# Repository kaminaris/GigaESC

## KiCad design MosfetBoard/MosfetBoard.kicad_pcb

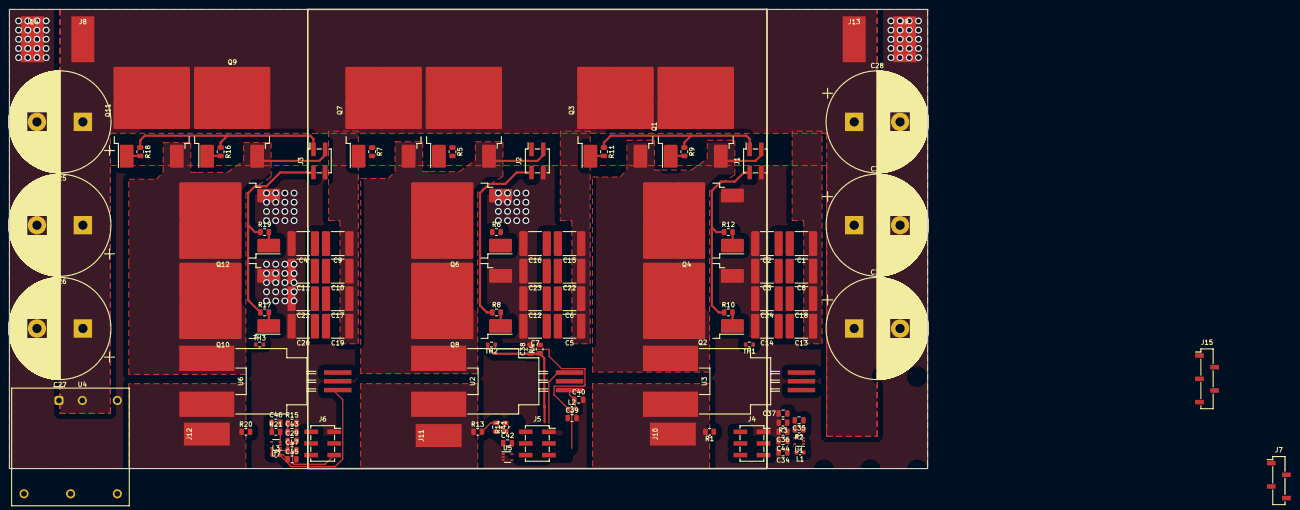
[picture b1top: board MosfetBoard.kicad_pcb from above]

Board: 2 copper layers, 200.0 x 100.0 mm, 106 parts (0 on the bottom side), 58 nets.

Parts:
C1, C2, C3, C4, C5, C6, C7, C8, C9, C10, C11, C12, C13, C14, C15, C16, C17, C18, C19, C20, C21, C22, C23, C24: C; C_2220_5650Metric
C25, C26, C27, C28, C30, C31: 680uF 200V; CP_Radial_D22.0mm_P10.00mm_SnapIn
C29, C35, C36, C39, C41, C42, C44, C46, C47: 100nF; C_0805_2012Metric
C34, C40, C45: 2.2u; C_0805_2012Metric
C37, C38, C43: 1u; C_0805_2012Metric
J1: DRIVER1; PinSocket_2x02_P2.54mm_Vertical_SMD
J2: DRIVER2; PinSocket_2x02_P2.54mm_Vertical_SMD
J3: DRIVER3; PinSocket_2x02_P2.54mm_Vertical_SMD
J4: PhaseConn1; PinSocket_2x03_P2.54mm_Vertical_SMD
J5: PhaseConn2; PinSocket_2x03_P2.54mm_Vertical_SMD
J6: PhaseConn3; PinSocket_2x03_P2.54mm_Vertical_SMD
J7: VINConn; PinSocket_1x04_P2.54mm_Vertical_SMD_Pin1Left
J8: BATT+Conn1; SolderWirePad_1x01_SMD_5x10mm
J9: BATT-Conn1; SolderWirePad_1x01_SMD_5x10mm
J10: A_PAD; SolderWirePad_1x01_SMD_5x10mm
J11: B_PAD; SolderWirePad_1x01_SMD_5x10mm
J12: C_PAD; SolderWirePad_1x01_SMD_5x10mm
J13: BATT+Conn2; SolderWirePad_1x01_SMD_5x10mm
J14: BATT-Conn2; SolderWirePad_1x01_SMD_5x10mm
J15: AuxConn; PinSocket_1x05_P2.54mm_Vertical_SMD_Pin1Left
L1, L2, L3: BLM18HE152SN1D; L_0603_1608Metric
Q1, Q2, Q3, Q4, Q5, Q6, Q7, Q8, Q9, Q10, Q11, Q12: IXTT220N20X4HV; TO-268-2
R1, R13, R20: 150k; R_0805_2012Metric
R2, R14, R21: 2.7k; R_0805_2012Metric
R3, R4, R15: 10k; R_0805_2012Metric
R5, R6, R7, R8, R9, R10, R11, R12, R16, R17, R18, R19: 2r2; R_0805_2012Metric
TH1, TH2, TH3: NCP18XH103F03RB; R_0603_1608Metric
U1, U5, U7: RS2166XC5; SOT-353_SC-70-5
U2, U3, U6: ACS773ECB-200B-PFF-T; Allegro_CB_SMD
U4: RDE20110S12; Converter_DCDC_TRACO_THN30-xxxx_THT

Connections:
+3.3V: C29.1, C36.1, C39.1, C42.1, C44.1, C47.1, J4.5, J5.5, J6.5, L1.1, L2.1, L3.1, TH1.1, TH2.1, TH3.1, U1.5 (VCC), U5.5 (VCC), U7.5 (VCC)
+12V: J7.3, J7.4
+BATT: C1.1, C5.1, C6.1, C8.1, C9.1, C10.1, C13.1, C15.1, C17.1, C18.1, C19.1, C22.1, C25.1, C26.1, C27.1, C28.1, C30.1, C31.1, J8.1, J13.1, Q1.2 (D), Q3.2 (D), Q5.2 (D), Q7.2 (D), Q9.2 (D), Q11.2 (D), U4.1 (+Vin)
-BATT: C2.2, C3.2, C4.2, C7.2, C11.2, C12.2, C14.2, C16.2, C20.2, C21.2, C23.2, C24.2, C25.2, C26.2, C27.2, C28.2, C29.2, C30.2, C31.2, C34.2, C36.2, C37.2, C38.2, C39.2, C40.2, C42.2, C43.2, C44.2, C45.2, C47.2, J1.4, J2.4, J3.4, J4.1, J5.1, J6.1, J7.1, J7.2, J9.1, J14.1, J15.1, Q2.3 (S), Q4.3 (S), Q6.3 (S), Q8.3 (S), Q10.3 (S), Q12.3 (S), R2.2, R3.2, R4.2, R14.2, R15.2, R21.2, U1.2 (D), U1.3 (GND), U2.2 (GND), U3.2 (GND), U4.2 (-Vin), U5.2 (D), U5.3 (GND), U6.2 (GND), U7.2 (D), U7.3 (GND)
A: J10.1, R1.1, U3.5 (IP-)
B: J11.1, R13.1, U2.5 (IP-)
C: J12.1, R20.1, U6.5 (IP-)
CURR1: J4.6, U3.3 (VIOUT)
CURR2: J5.6, U2.3 (VIOUT)
CURR3: J6.6, U6.3 (VIOUT)
MOSTEMP1: C37.1, J4.4, R3.1, TH1.2
MOSTEMP2: C38.1, J5.4, R4.1, TH2.2
MOSTEMP3: C43.1, J6.4, R15.1, TH3.2
unnamed: C1.2, C2.1
unnamed: C3.1, C8.2
unnamed: C4.1, C9.2
unnamed: C5.2, C7.1
unnamed: C10.2, C11.1
unnamed: C6.2, C12.1
unnamed: C13.2, C14.1
unnamed: C15.2, C16.1
unnamed: C17.2, C21.1
unnamed: C18.2, C24.1
unnamed: C19.2, C20.1
unnamed: C22.2, C23.1
unnamed: Q1.1 (G), R9.2
unnamed: Q2.1 (G), R10.2
unnamed: Q3.1 (G), R11.2
unnamed: Q4.1 (G), R12.2
unnamed: Q5.1 (G), R5.2
unnamed: Q6.1 (G), R6.2
unnamed: Q7.1 (G), R7.2
unnamed: Q8.1 (G), R8.2
unnamed: Q9.1 (G), R16.2
unnamed: Q10.1 (G), R17.2
unnamed: Q11.1 (G), R18.2
unnamed: Q12.1 (G), R19.2
unnamed: C35.2, U1.1 (S)
unnamed: C40.1, L2.2, U2.1 (VCC)
unnamed: C34.1, L1.2, U3.1 (VCC)
unnamed: C41.2, U5.1 (S)
unnamed: C45.1, L3.2, U6.1 (VCC)
unnamed: C46.2, U7.1 (S)
PH1: J1.1, R9.1, R11.1
PH2: J2.1, R5.1, R7.1
PH3: J3.1, R16.1, R18.1
PHASE1: J1.3, Q1.3 (S), Q2.2 (D), Q3.3 (S), Q4.2 (D), U3.4 (IP+)
PHASE2: J2.3, Q5.3 (S), Q6.2 (D), Q7.3 (S), Q8.2 (D), U2.4 (IP+)
PHASE3: J3.3, Q9.3 (S), Q10.2 (D), Q11.3 (S), Q12.2 (D), U6.4 (IP+)
PL1: J1.2, R10.1, R12.1
PL2: J2.2, R6.1, R8.1
PL3: J3.2, R17.1, R19.1
SENS_FILTER_ENABLE1: J4.3, U1.4 (SEL)
SENS_FILTER_ENABLE2: J5.3, U5.4 (SEL)
SENS_FILTER_ENABLE3: J6.3, U7.4 (SEL)
VSENSE1: C35.1, J4.2, R1.2, R2.1
VSENSE2: C41.1, J5.2, R13.2, R14.1
VSENSE3: C46.1, J6.2, R20.2, R21.1

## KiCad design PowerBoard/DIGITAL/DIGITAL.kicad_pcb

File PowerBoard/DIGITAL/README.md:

# Power Supply DIGITAL

## ⚠ Not working - Do not use ⚠

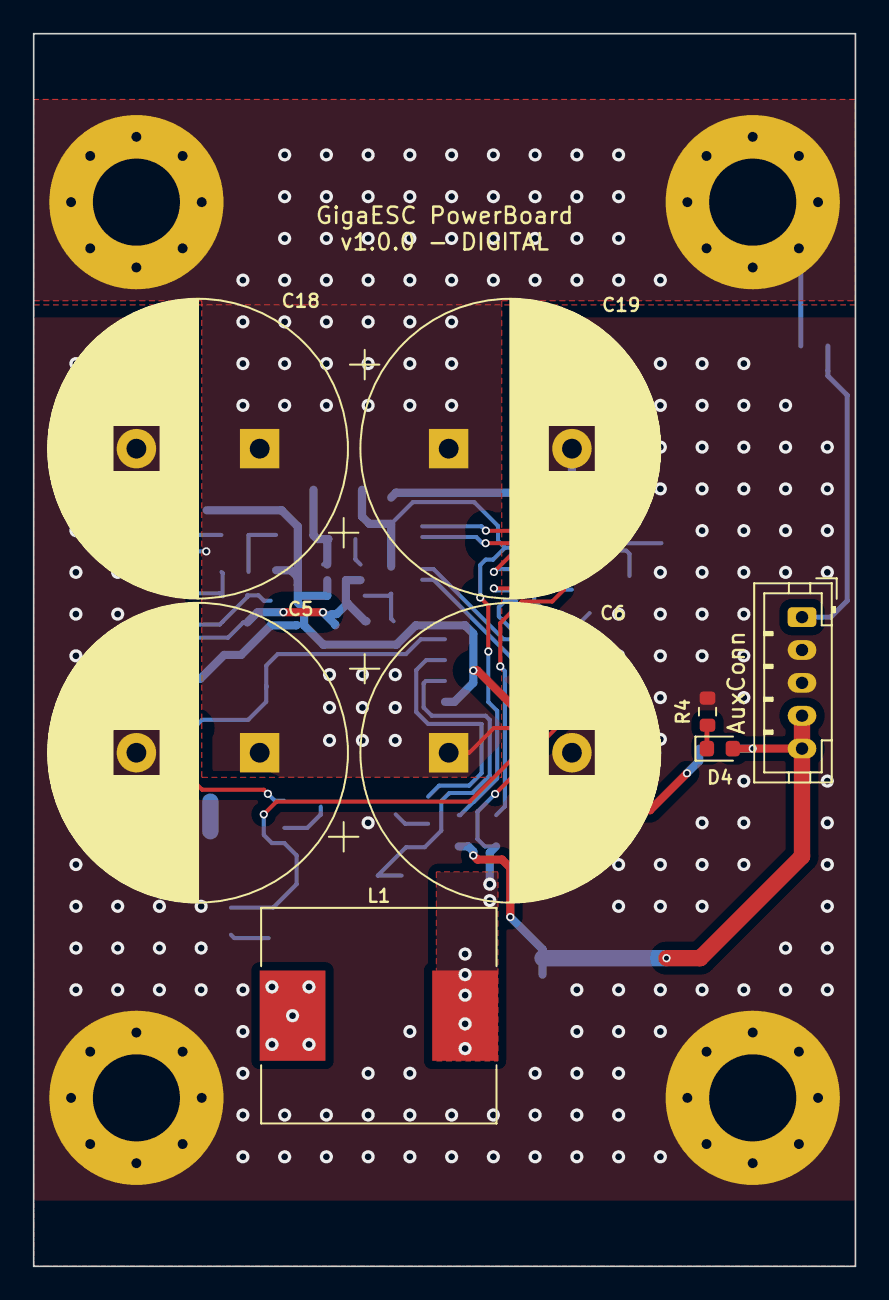
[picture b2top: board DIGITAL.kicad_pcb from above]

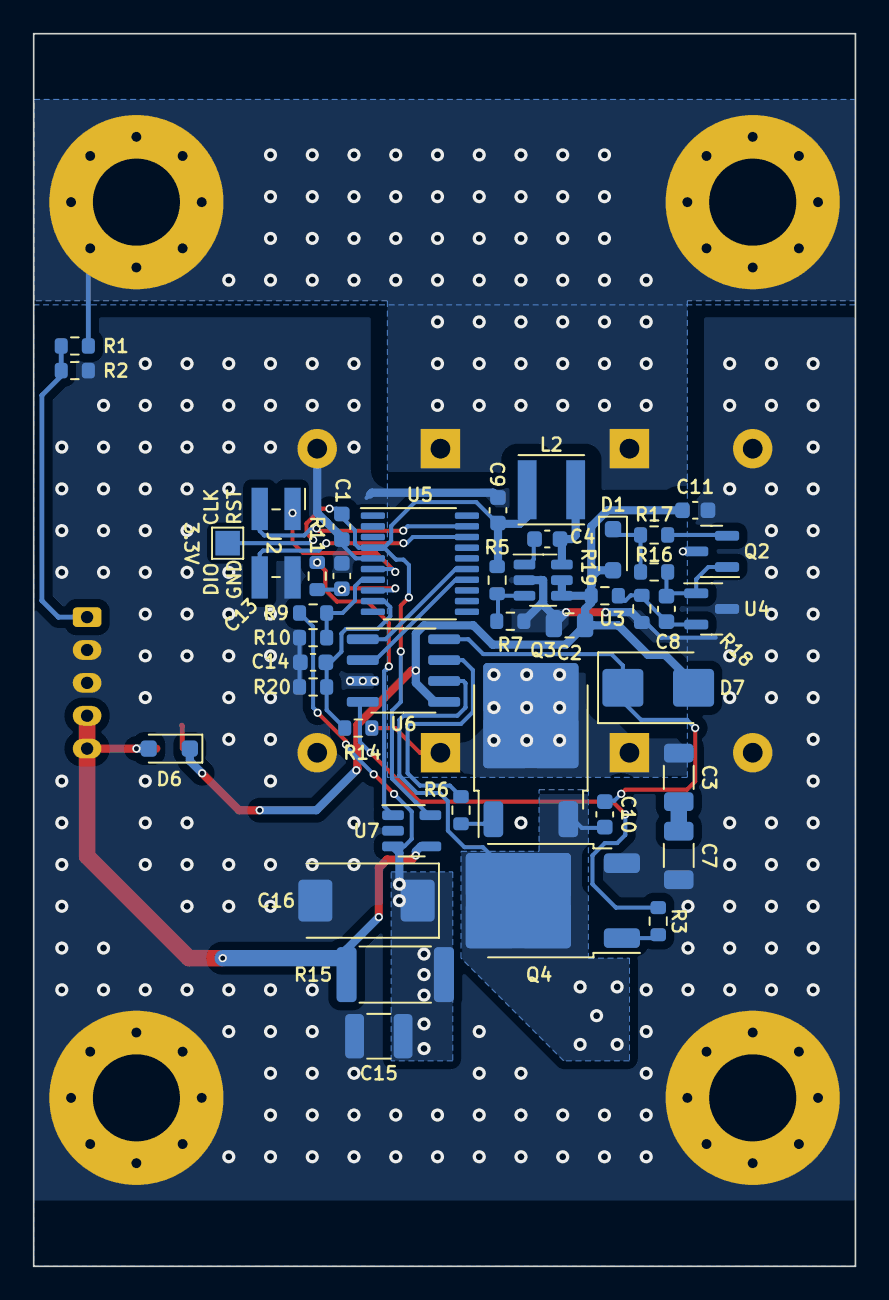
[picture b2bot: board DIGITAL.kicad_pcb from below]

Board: 2 copper layers, 50.0 x 75.0 mm, 55 parts (43 on the bottom side), 31 nets.

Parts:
C1, C10: 100n; C_0603_1608Metric
C2: 4.7u; C_0805_2012Metric
C3, C7: 2.2u 100V; C_1206_3216Metric
C4: 22n; C_0603_1608Metric
C5, C6, C18, C19: 330u 200V; CP_Radial_D18.0mm_P7.50mm
C8: 1n; C_0603_1608Metric
C9: 22u; C_0603_1608Metric
C11: 1u; C_0603_1608Metric
C13, C14: 10n; C_0603_1608Metric
C15: 47u 16V; C_1210_3225Metric
C16: 100uF 16V; CP_EIA-7343-31_Kemet-D
D1: BZT52C5V1S; D_SOD-323_HandSoldering
D4: RUN; D_0603_1608Metric
D6: 1N5819WS; D_SOD-323_HandSoldering
D7: SS520BF; D_SMB
H1, H2, H3, H4: MountingHole_Pad; MountingHole_5.3mm_M5_Pad_Via
J1: AuxConn; JST_PH_B5B-PH-K_1x05_P2.00mm_Vertical
J2: Conn_02x02_Counter_Clockwise; JTAG_SMD
L1: 100uH; L_Chilisin_BMRG00131360
L2: 22uH; L_Vishay_IFSC-1515AH_4x4x1.8mm
Q2: BSS126; SOT-23
Q3, Q4: IRFR13N20DTRPBF; TO-252-2
R1: 150k; R_0603_1608Metric
R2: 2.7k; R_0603_1608Metric
R3, R6: 4.7; R_0603_1608Metric
R4: 82k; R_0603_1608Metric
R5: 100k; R_0603_1608Metric
R7: 22k; R_0603_1608Metric
R9, R16, R18, R20: 10k; R_0603_1608Metric
R10: 2.2k; R_0603_1608Metric
R11: 47; R_0603_1608Metric
R14: 1M; R_0603_1608Metric
R15: 0.01; R_2512_6332Metric
R17: 100; R_0603_1608Metric
R19: 30k; R_0603_1608Metric
TP1: 3.3V; TestPoint_Pad_1.5x1.5mm
U3: MT2492; SOT-23-6
U4: TL431DBZ; SOT-23
U5: STM32G030F6Px; TSSOP-20_4.4x6.5mm_P0.65mm
U6: IR2181; SOIC-8_3.9x4.9mm_P1.27mm
U7: INA180A2; SOT-23-5

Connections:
+3.3V: C1.1, C9.1, L2.2, R5.2, TP1.1, U5.4 (VDD), U7.5 (V+)
+12V: D4.2 (A), D6.2 (A), J1.4, J1.5, R15.1, U7.4 (-)
+BATT: C3.1, C5.1, C6.1, C18.1, C19.1, H2.1, H4.1, Q2.3 (D), Q3.2 (D), R1.1, R14.2
-BATT: C1.2, C2.2, C5.2, C6.2, C7.2, C9.2, C11.2, C13.2, C14.2, C15.2, C16.2, C18.2, C19.2, H1.1, H3.1, J1.2, J1.3, J2.2, Q4.3 (S), R2.2, R4.1, R7.1, R10.1, R18.1, R20.1, U3.2 (GND), U4.3 (A), U5.5 (VSS), U6.3 (COM), U7.2 (GND)
BOOTSTRAP: C2.1, C11.1, D1.2 (A), D6.1 (K), D7.2 (A), R19.2, U3.4 (EN), U3.5 (VIN), U6.5 (VCC)
H: U5.15 (PB0/PB1/PB2/PA8), U6.1 (HIN)
IN_V: J1.1, R1.2, R2.1
IoutFB: R11.2, U7.1
L: U5.14 (PA7), U6.2 (LIN)
unnamed: C3.2, C7.1
unnamed: D1.1 (K), R16.1, R17.1
unnamed: D4.1 (K), R4.2
unnamed: C10.1, D7.1 (K), U6.8 (VB)
unnamed: C8.1, Q2.1 (G), R16.2, U4.1 (K)
unnamed: Q2.2 (S), R17.2
unnamed: Q3.1 (G), R6.2
unnamed: C10.2, L1.1, Q3.3 (S), Q4.2 (D), U6.6 (VS)
unnamed: Q4.1 (G), R3.2
unnamed: C4.1, U3.1 (BST)
unnamed: R5.1, R7.2, U3.3 (FB)
unnamed: C4.2, L2.1, U3.6 (LX)
unnamed: C8.2, R18.2, R19.1, U4.2 (REF)
unnamed: C13.1, R11.1, U5.8 (PA1)
unnamed: R6.1, U6.7 (HO)
unnamed: R3.1, U6.4 (LO)
unnamed: C15.1, C16.1, L1.2, R9.2, R15.2, U7.3 (+)
RESET: J2.1, U5.6 (NRST)
SWCLK: J2.3, U5.19 (PA14/PA15)
SWDIO: J2.4, U5.18 (PA13)
VinFB: C14.1, R14.1, R20.2, U5.9 (PA2)
VoutFB: R9.1, R10.2, U5.7 (PA0)

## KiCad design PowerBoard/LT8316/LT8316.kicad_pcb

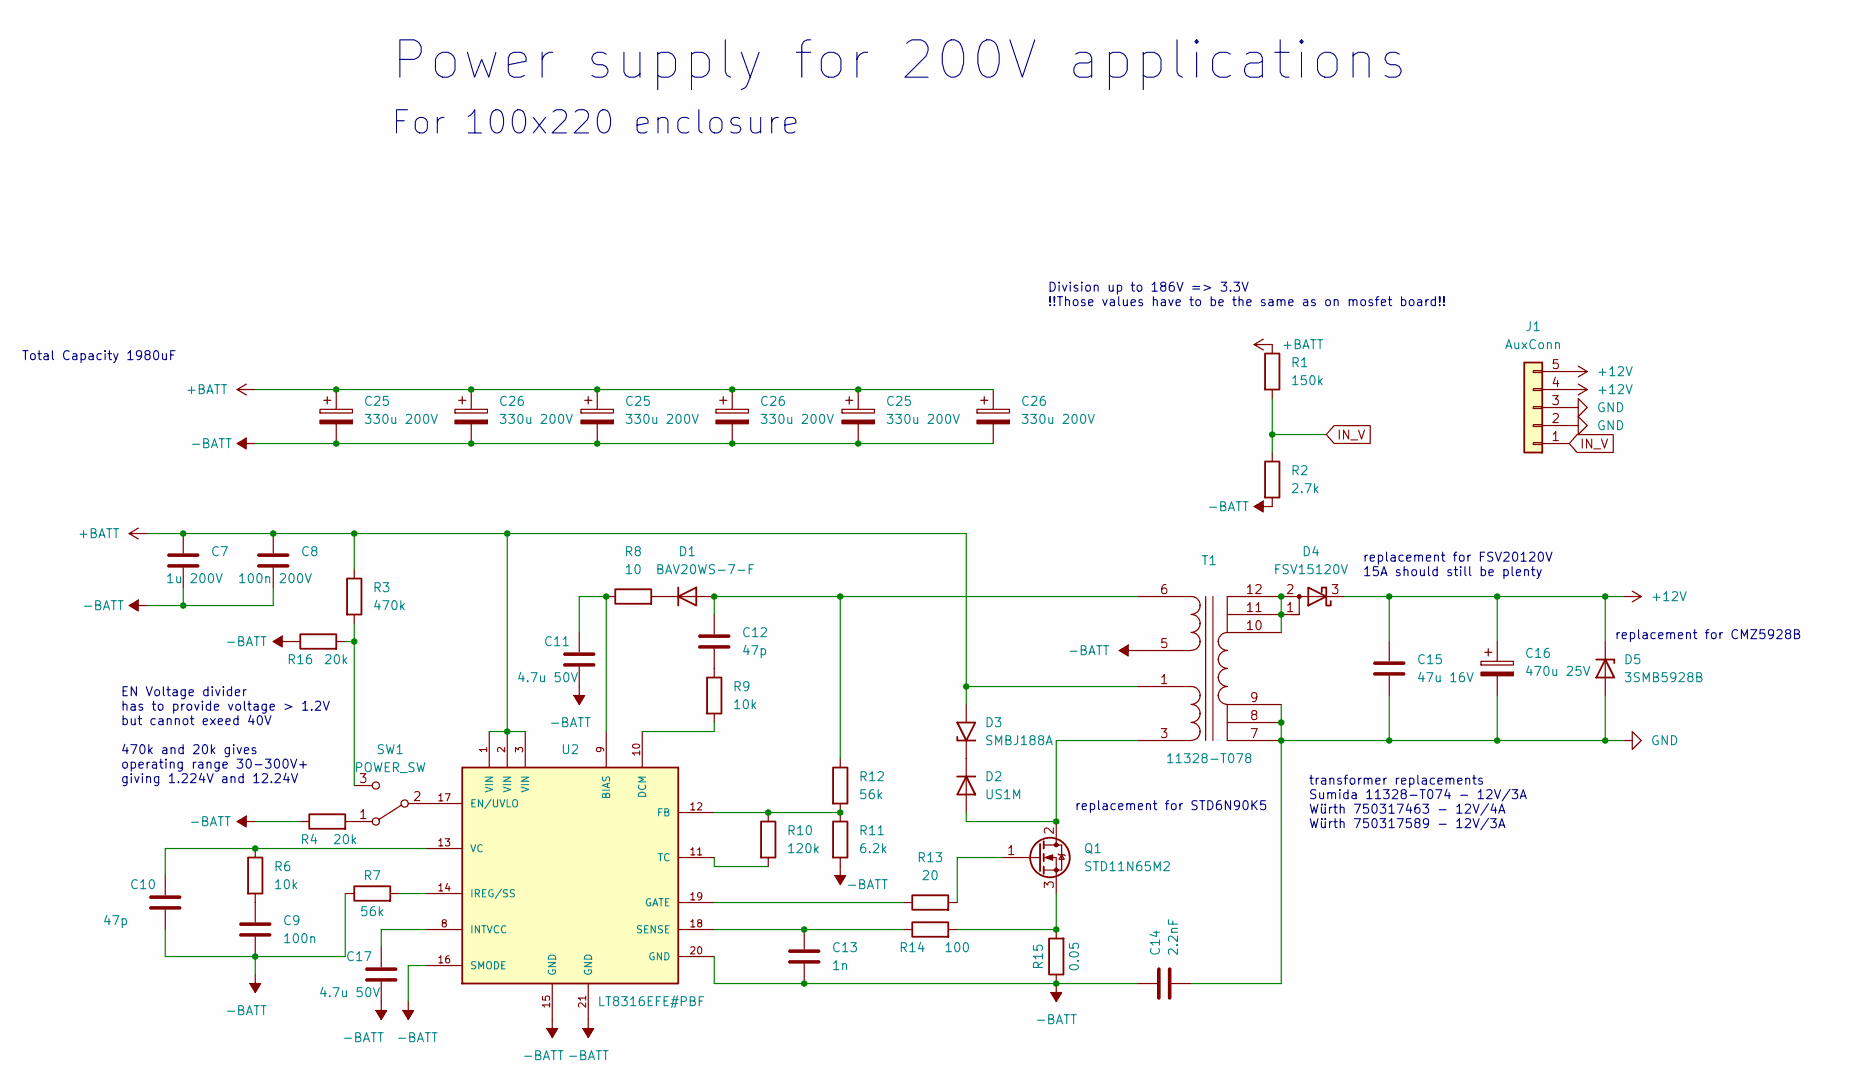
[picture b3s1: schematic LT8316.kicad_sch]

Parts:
C7: 1u 200V; C_2220_5650Metric; MPN C78775; Mouser 81-GRM55DR72D105KW1L
C8: 100n 200V; C_1206_3216Metric; MPN C113894; Mouser 810-CGJ4J3X7T2D104K
C9: 100n; C_0603_1608Metric_L; MPN C14663; Mouser 581-08055C104KAT4A
C10: 47p; C_0603_1608Metric_L; MPN C1671; Mouser 603-CC805JRNPO9BN470
C11, C17: 4.7u 50V; C_1206_3216Metric; MPN C29823; Mouser 963-UMK316AB7475ML-T
C12: 47p; C_0603_1608Metric_L; MPN C1671; Mouser 80-C0603C470K1GAUTO
C13: 1n; C_0603_1608Metric; MPN C1588; Mouser 80-C0603C102K5R7081
C14: 2.2nF; C_0603_1608Metric; MPN C1604; Mouser 603-CC805KRX7R0BB222
C15: 47u 16V; C_1210_3225Metric; MPN C2918513; Mouser 81-GRM32EC81C476KE5K
C16: 470u 25V; CP_Elec_10x10.5; MPN C5162351; Mouser 667-EEE-1EA471P
C25, C26: 330u 200V; CP_Radial_D18.0mm_P7.50mm; MPN C697601; Mouser 661-EKMR201VS222MR50
D1: BAV20WS-7-F; D_SOD-323; MPN C151448; Mouser 621-BAV20WS-F
D2: US1M; D_SMA; MPN C412437; Mouser 78-US1M-M35AT
D3: SMBJ188A; D_SMB; MPN C908808; Mouser 576-SMBJ188A
D4: FSV15120V; TO-277A; MPN C463273; Mouser 512-FSV15120V
D5: 3SMB5928B; D_SMB; MPN C2983224; Mouser 821-1SMB5928
J1: AuxConn; JST_XH_B5B-XH-A_1x05_P2.50mm_Vertical; MPN C161870
Q1: STD11N65M2; TO-252-2; MPN C500947; JLCRotOffset 0
R1: 150k; R_0603_1608Metric; MPN C22807; Mouser 603-RC0805FR-07100KL
R2: 2.7k; R_0603_1608Metric; MPN C13167; Mouser 71-CRCW0805-1.8K-E3
R3: 470k; R_0603_1608Metric; MPN C23178; Mouser 71-CRCW1206499KFKEB
R4, R16: 20k; R_0603_1608Metric; MPN C4184; Mouser 71-CRCW080520K0FKEB
R6: 10k; R_0603_1608Metric; MPN C25804; Mouser 603-AC0805JR-0710KL
R7: 56k; R_0603_1608Metric; MPN C17756; Mouser 652-CR0603FX-5622ELF
R8: 10; R_0603_1608Metric; MPN C22859; Mouser 603-AF0603FR-0710RL
R9: 10k; R_0603_1608Metric; MPN C25804; Mouser 756-WCR0603-10KFI
R10: 120k; R_0603_1608Metric; MPN C25808; Mouser 660-RK73H2ATTD1213F
R11: 6.2k; R_0603_1608Metric; MPN C4260; Mouser 667-ERJ-6ENF4991V
R12: 56k; R_0603_1608Metric; MPN C23206; Mouser 603-RC0805FR-0744K2L
R13: 20; R_0603_1608Metric; MPN C22950; Mouser 71-CRCW080520R0FKEAC
R14: 100; R_0603_1608Metric; MPN C22775; Mouser 791-WR08X1000FTL
R15: 0.05; R_2512_6332Metric; MPN C2874774; Mouser 708-CSM2512FT50L0
SW1: POWER_SW; JST_XH_B3B-XH-A_1x03_P2.50mm_Vertical; MPN C144394
T1: 11328-T078; PQ2620; MPN C7423050; Mouser 851-11328-T078
U2: LT8316EFE#PBF; IC_LT8316EFE#PBF; PARTREV A; Mouser 584-LT8316EFE#PBF

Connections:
+12V: C15.1, C16.1, D4.3 (K), D5.1 (K), J1.4, J1.5
+BATT: C7.1, C8.1, D3.2 (A2), R1.1, R3.1, T1.1 (IN+), U2.1 (VIN), U2.2 (VIN), U2.3 (VIN); also elsewhere on the board
-BATT: C7.2, C8.2, C9.2, C10.2, C11.2, C13.2, C14.1, C17.2, R2.2, R4.1, R7.1, R11.2, R15.1, R16.1, T1.5 (OUT1B), U2.15 (GND), U2.16 (SMODE), U2.20 (GND), U2.21 (GND); also elsewhere on the board
GND: C14.2, C15.2, C16.2, D5.2 (A), J1.2, J1.3, T1.7 (OUT2B), T1.8 (PM), T1.9 (PM)
IN_V: J1.1, R1.2, R2.1
unnamed: C9.1, R6.2
unnamed: C12.2, R9.1
unnamed: C12.1, D1.2 (A), R12.1, T1.6 (OUT2A)
unnamed: D1.1 (K), R8.2
unnamed: D2.2 (A), Q1.2 (D), T1.3 (IN-)
unnamed: D2.1 (K), D3.1 (A1)
unnamed: D4.1 (A), D4.2 (A), T1.10 (PM), T1.11 (PM), T1.12 (PM)
unnamed: Q1.1 (G), R13.2
unnamed: Q1.3 (S), R14.2, R15.2
unnamed: R4.2, SW1.1 (A)
unnamed: SW1.2 (B), U2.17 (EN/UVLO)
unnamed: R3.2, R16.2, SW1.3 (C)
unnamed: C11.1, R8.1, U2.9 (BIAS)
unnamed: R9.2, U2.10 (DCM)
unnamed: R10.1, R11.1, R12.2, U2.12 (FB)
unnamed: R13.1, U2.19 (GATE)
unnamed: C17.1, U2.8 (INTVCC)
unnamed: R7.2, U2.14 (IREG/SS)
unnamed: C13.1, R14.1, U2.18 (SENSE)
unnamed: R10.2, U2.11 (TC)
unnamed: C10.1, R6.1, U2.13 (VC)

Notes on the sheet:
Power supply for 200V applications
transformer replacements Sumida 11328-T074 - 12V/3A Würth 750317463 - 12V/4A Würth 750317589 - 12V/3A
replacement for FSV20120V 15A should still be plenty
replacement for STD6N90K5
Total Capacity 1980uF
EN Voltage divider has to provide voltage > 1.2V but cannot exeed 40V 470k and 20k gives operating range 30-300V+ giving 1.224V and 12.24V
Division up to 186V => 3.3V !!Those values have to be the same as on mosfet board!!
replacement for CMZ5928B
For 100x220 enclosure

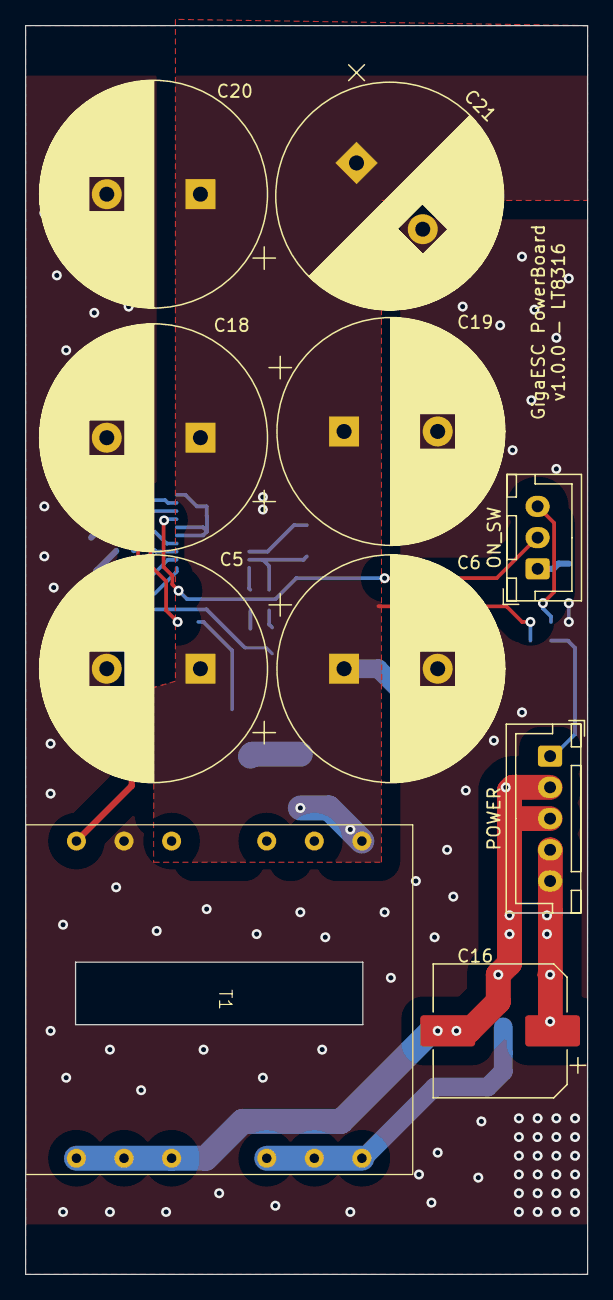
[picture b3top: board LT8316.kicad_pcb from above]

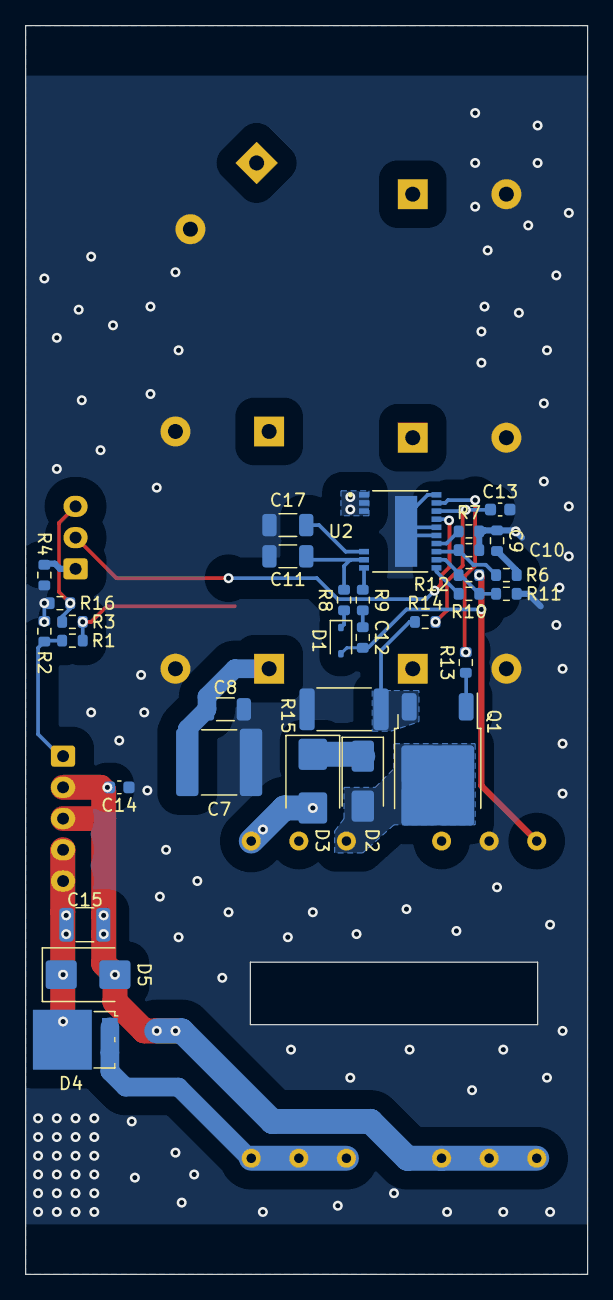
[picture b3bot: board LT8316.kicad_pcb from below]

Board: 2 copper layers, 45.0 x 100.0 mm, 42 parts (32 on the bottom side), 26 nets.

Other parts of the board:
C5, C6, C18, C19, C20, C21: 330u 200V; CP_Radial_D18.0mm_P7.50mm

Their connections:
+BATT: C5.1, C6.1, C18.1, C19.1, C20.1, C21.1; also elsewhere on the board
-BATT: C5.2, C6.2, C18.2, C19.2, C20.2, C21.2; also elsewhere on the board

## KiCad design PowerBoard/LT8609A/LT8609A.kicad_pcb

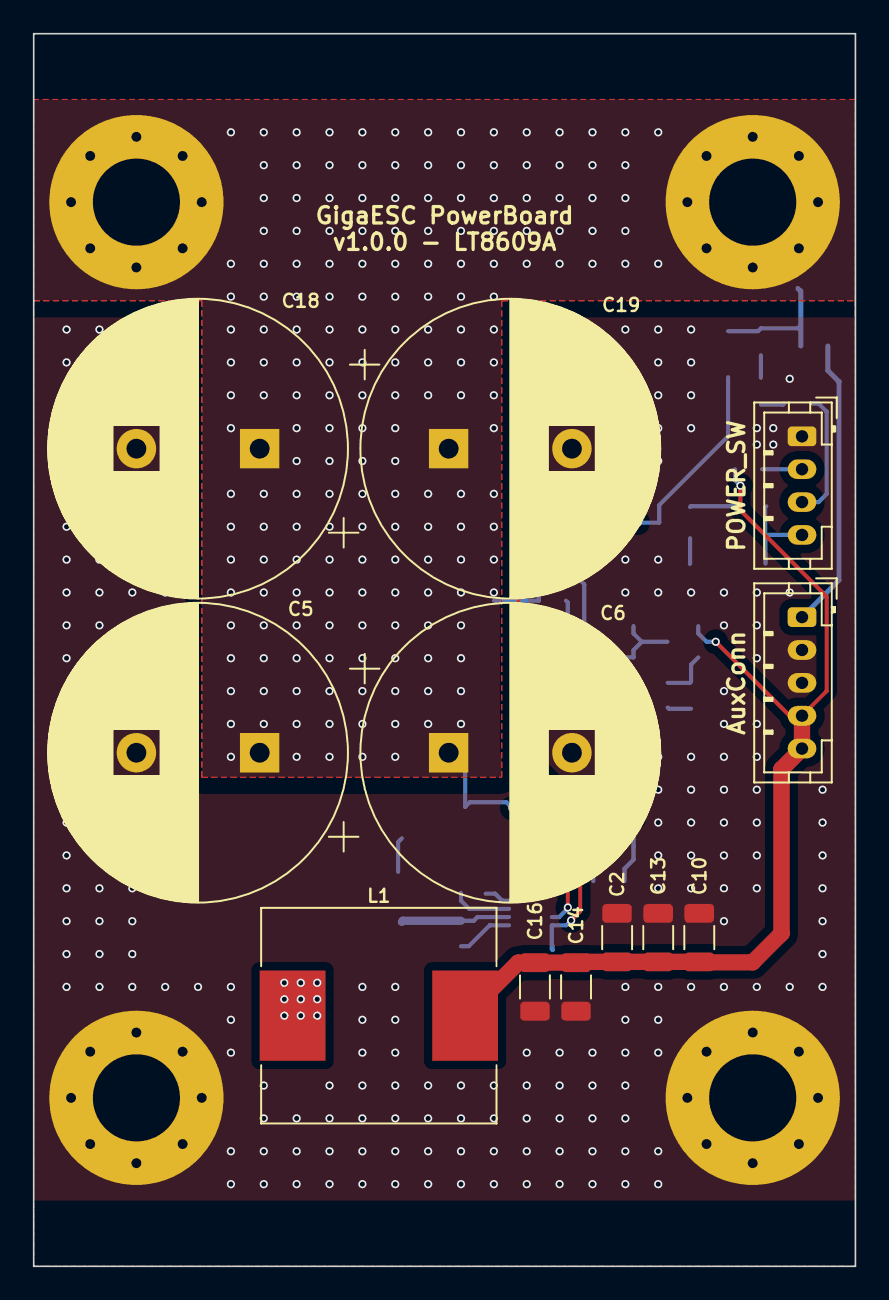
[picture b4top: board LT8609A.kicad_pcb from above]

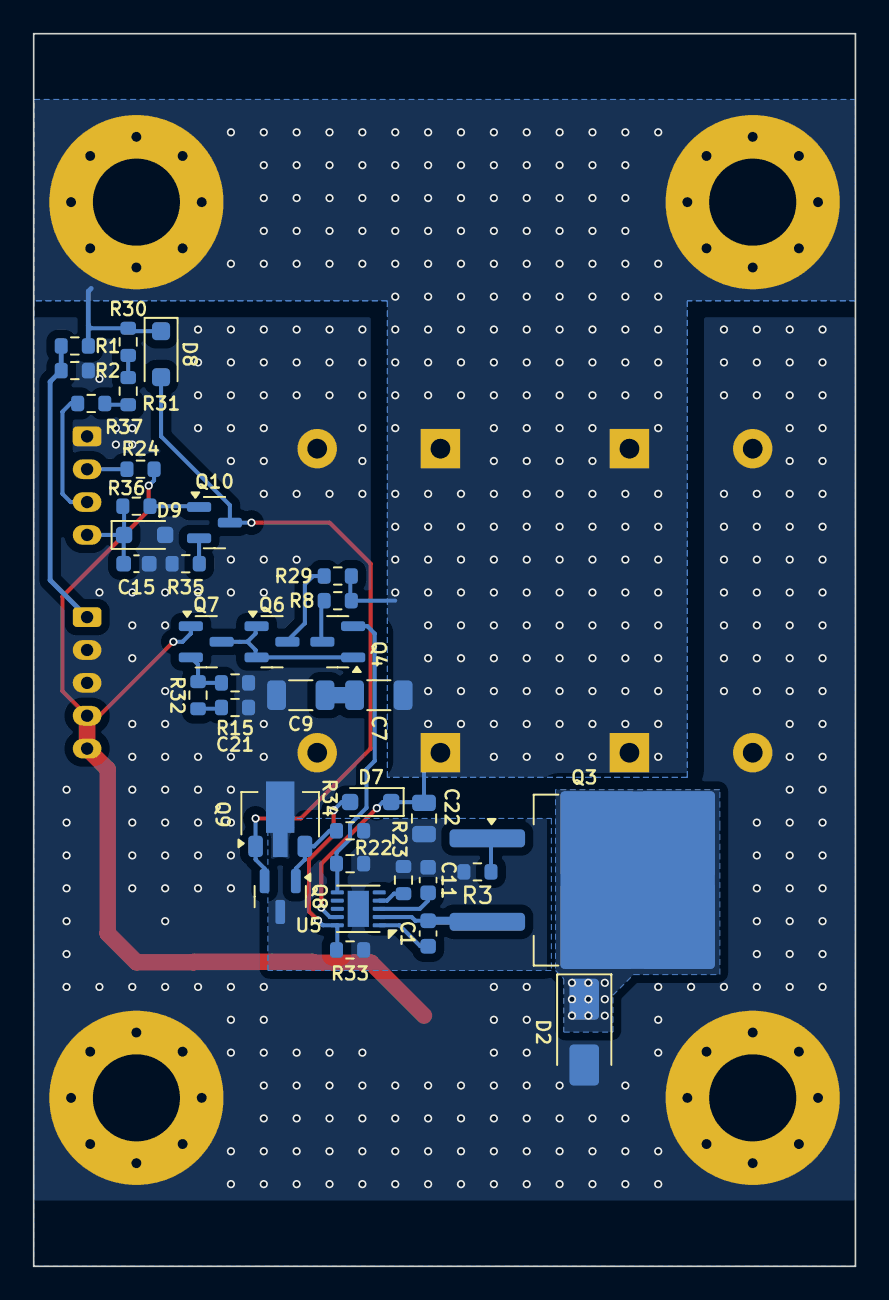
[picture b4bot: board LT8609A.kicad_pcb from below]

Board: 2 copper layers, 50.0 x 75.0 mm, 52 parts (36 on the bottom side), 28 nets.

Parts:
C1, C15: 100n; C_0603_1608Metric
C2, C10, C13, C14, C16: 22u; C_1206_3216Metric
C5, C6, C18, C19: 330u 200V; CP_Radial_D18.0mm_P7.50mm
C7, C9: 2.2u 100V; C_1206_3216Metric
C11: 1u; C_0603_1608Metric
C21: 22n; C_0603_1608Metric_L
C22: 10u; C_0805_2012Metric
D2: SS520F; D_SMA
D7, D9: BZT52C8V2S; D_SOD-323_HandSoldering
D8: BZT52B12; D_SOD-123F
H1, H2, H3, H4: MountingHole_Pad; MountingHole_5.3mm_M5_Pad_Via
J1: AuxConn; JST_PH_B5B-PH-K_1x05_P2.00mm_Vertical
J2: POWER_SW; JST_PH_B4B-PH-K_1x04_P2.00mm_Vertical
L1: 100uH; L_Chilisin_BMRG00131360
Q3: IRF9640SPBF; TO-263-2
Q4, Q6, Q8: S9012 2T1; SOT-23
Q7, Q10: MMBTA42; SOT-23
Q9: MMBTA92T; SOT-89-3
R1: 150k; R_0603_1608Metric
R2: 2.7k; R_0603_1608Metric
R3: 22; R_0603_1608Metric
R8, R29: 1k; R_0603_1608Metric
R15, R33: 10k; R_0603_1608Metric
R22, R32: 820; R_0603_1608Metric
R23: 220k; R_0603_1608Metric
R24, R30, R31, R37: 100k; R_0603_1608Metric
R34: 150; R_0603_1608Metric
R35: 4.7k; R_0603_1608Metric
R36: 30k; R_0603_1608Metric
U5: LT8609AJDDM; DFN-10-1EP_2.6x2.6mm_P0.5mm_EP1.3x2.2mm

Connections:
+12V: C2.1, C10.1, C13.1, C14.1, C16.1, J1.4, J1.5, L1.2, Q7.1 (B), R24.2
+BATT: C5.1, C6.1, C7.1, C18.1, C19.1, C22.1, D7.1 (K), D8.1 (K), H2.1, H4.1, R1.1, R8.2, R29.2, R30.1, U5.9 (VIN)
-BATT: C2.2, C5.2, C6.2, C9.2, C10.2, C13.2, C14.2, C15.1, C16.2, C18.2, C19.2, C21.2, D2.2 (A), D9.2 (A), H1.1, H3.1, J1.2, J1.3, J2.1, Q9.2 (C), R2.2, R15.1, R35.2
GNDH: C11.2, C22.2, Q8.3 (E), R3.2, R22.1, R23.2, R33.1, R34.1, U5.11 (GND)
IN_V: J1.1, R1.2, R2.1
unnamed: C7.2, C9.1
unnamed: C21.1, R32.1
unnamed: D2.1 (K), L1.1, Q3.2 (D)
unnamed: D7.2 (A), R33.2, U5.10 (EN/UV)
unnamed: D8.2 (A), Q8.2 (C), Q9.1 (B), Q10.3 (C)
unnamed: C15.2, D9.1 (K), J2.4, R36.1
unnamed: J2.2, R24.1
unnamed: J2.3, R37.2
unnamed: Q3.1 (G), R3.1
unnamed: C1.1, Q3.3 (S), U5.2 (SW)
unnamed: Q4.1 (B), Q6.1 (B), Q6.2 (C), Q7.3 (C)
unnamed: Q4.2 (C), R22.2, U5.6 (FB)
unnamed: Q4.3 (E), R8.1
unnamed: Q6.3 (E), R29.1
unnamed: Q7.2 (E), R15.2, R32.2
unnamed: Q8.1 (B), Q9.3 (E), R34.2
unnamed: Q10.1 (B), R36.2
unnamed: Q10.2 (E), R35.1
unnamed: R30.2, R31.1
unnamed: R31.2, R37.1
unnamed: C1.2, U5.1 (BST)
unnamed: C11.1, U5.3 (INTVCC)
unnamed: R23.1, U5.4 (RT)

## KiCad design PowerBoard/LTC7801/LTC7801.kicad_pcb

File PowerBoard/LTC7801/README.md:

# Power Supply LTC7801

## ⚠ Not working - Do not use ⚠

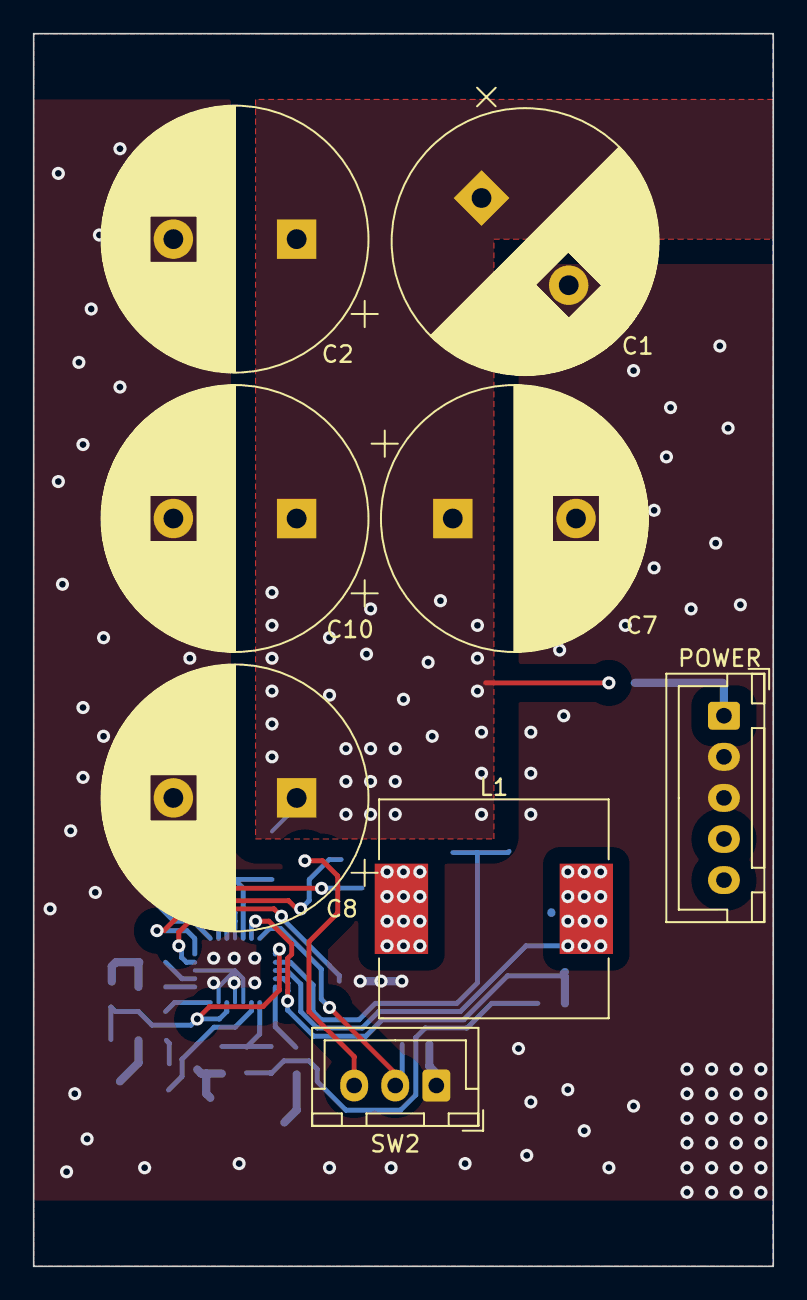
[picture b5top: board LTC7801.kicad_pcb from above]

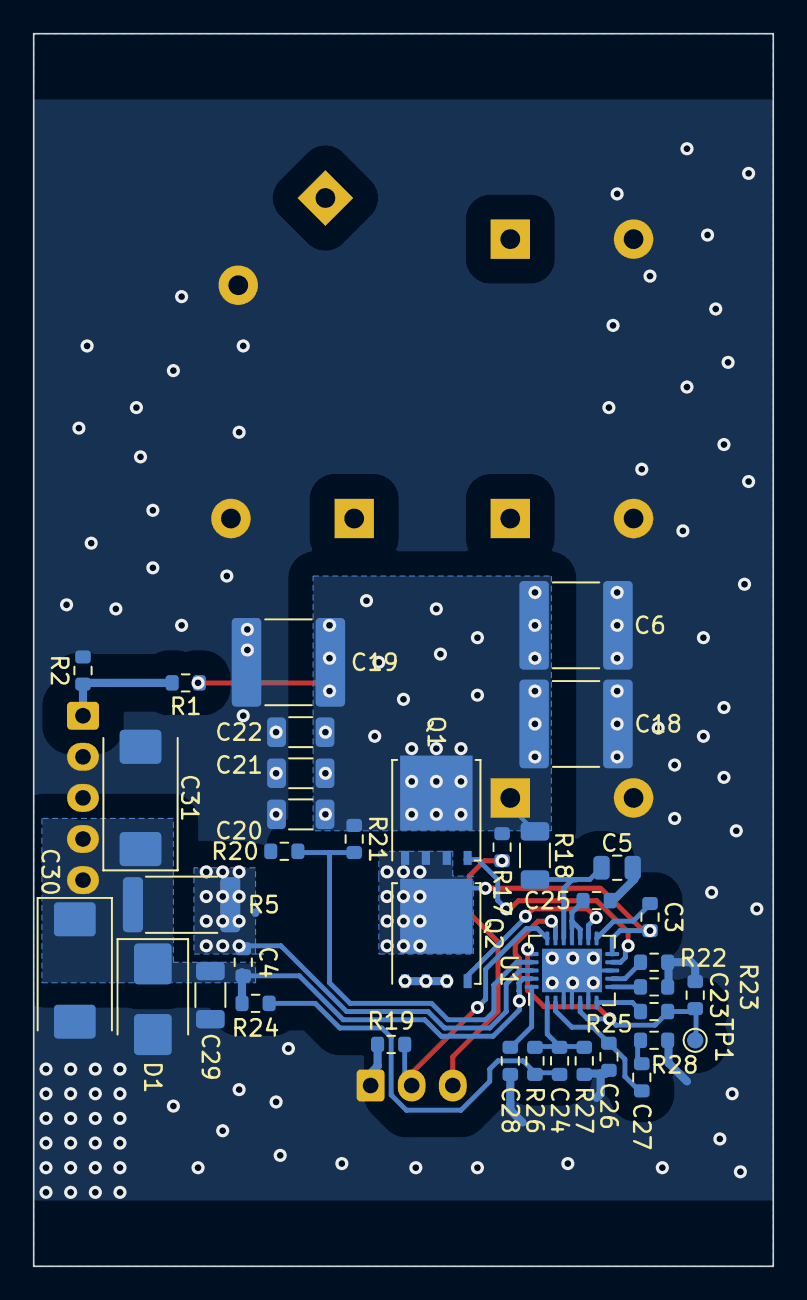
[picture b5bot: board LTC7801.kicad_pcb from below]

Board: 2 copper layers, 45.0 x 75.0 mm, 46 parts (38 on the bottom side), 23 nets.

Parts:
C1, C2, C7, C8, C10: 330u 150V; CP_Radial_D16.0mm_P7.50mm
C3, C23, C28: 100n; C_0603_1608Metric_L
C4: 1n; C_0603_1608Metric_L
C5: 100n 200V; C_0805_2012Metric
C6, C18, C19: 1u 200V; C_2220_5650Metric
C20, C21, C22: 470n 200V; C_1206_3216Metric
C24: 10pF; C_0603_1608Metric_L
C25: 4.7u 50V; C_0603_1608Metric_L
C26: 100p; C_0603_1608Metric_L
C27: 4.7n; C_0603_1608Metric_L
C29: 22uF; R_1206_3216Metric
C30, C31: 150u 16V; CP_EIA-7343-31_Kemet-D
D1: 3SMB5928B; D_SMB
J1: AuxConn; JST_XH_B5B-XH-A_1x05_P2.50mm_Vertical
L1: 100MHz 33uH 5A; L_Sunlord_MWSA1204S-220
Q1: BSC520N15NS3; TDSON-8-1
Q2: BSC110N15NS5; TDSON-8-1
R1, R17, R19, R25: 100k; R_0603_1608Metric
R2: 1.8k; R_0603_1608Metric
R5: 0.006; R_2512_6332Metric
R18: 10; R_1206_3216Metric
R20: 5.6k; R_0603_1608Metric
R21: 680k; R_0603_1608Metric
R22: 82k; R_0603_1608Metric
R23: 30k; R_0603_1608Metric
R24: 10 1%; R_0603_1608Metric
R26: 130k; R_0603_1608Metric
R27: 9.1k; R_0603_1608Metric
R28: 10k; R_0603_1608Metric
SW2: POWER_SW; JST_XH_B3B-XH-A_1x03_P2.50mm_Vertical
TP1: TestPoint; TestPoint_Pad_D1.0mm
U1: LTC7801EUFD#PBF; QFN-24-1EP_4x5mm_P0.5mm_EP2.65x3.65mm

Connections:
+12V: C4.2, C29.1, C30.1, C31.1, D1.1 (K), J1.4, J1.5, R5.2, R24.2, U1.18 (EXTVCC), U1.23 (SENSE–)
+BATT: C1.1, C2.1, C6.1, C7.1, C8.1, C10.1, C18.1, C19.1, C20.1, C21.1, C22.1, Q1.5 (D), R1.1, R17.1, R18.2, R21.1
-BATT: C1.2, C2.2, C5.1, C6.2, C7.2, C8.2, C10.2, C18.2, C19.2, C20.2, C21.2, C22.2, C23.1, C25.1, C26.2, C28.1, C29.2, C30.2, C31.2, D1.2 (A), J1.2, J1.3, Q2.1 (S), Q2.2 (S), Q2.3 (S), R2.2, R19.1, R20.2, R22.2, R23.2, R27.2, R28.2, SW2.1 (A), U1.3 (MODE), U1.4 (GND), U1.6 (PLLIN), U1.10 (DRVUV), U1.25 (GND)
IN_V: J1.1, R1.2, R2.1
unnamed: C24.1, R24.1, R26.1
unnamed: C27.2, R28.1
unnamed: Q1.4 (G), U1.11 (TG)
unnamed: C3.2, L1.1, Q1.1 (S), Q1.2 (S), Q1.3 (S), Q2.5 (D), U1.12 (SW)
unnamed: Q2.4 (G), U1.14 (BG)
unnamed: R19.2, SW2.2 (B), U1.19 (RUN)
unnamed: R17.2, SW2.3 (C)
unnamed: C3.1, U1.13 (BOOST)
unnamed: C23.2, R25.1, TP1.1, U1.5 (CPUMP_EN), U1.20 (INTVCC)
unnamed: C25.2, U1.15 (DRVCC), U1.16 (NDRV)
unnamed: R22.1, U1.9 (DRVSET)
unnamed: R23.1, U1.8 (FREQ)
unnamed: C26.1, C27.1, U1.2 (ITH)
unnamed: R20.1, R21.2, U1.21 (OVLO)
unnamed: R25.2, U1.7 (PGOOD)
unnamed: C28.2, U1.24 (SS)
unnamed: C24.2, R26.2, R27.1, U1.1 (VFB)
unnamed: C5.2, R18.1, U1.17 (VIN)
SENSE+: C4.1, L1.2, R5.1, U1.22 (SENSE+)
